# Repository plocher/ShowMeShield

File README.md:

# ShowMeShield
## License: Creative Commons Attribution-ShareAlike 2.0 Generic (CC BY-SA 2.0)

Arduino IO pin LEDs on wings

Features
  * increased board size from 5cmX5cm to 3.5"x2" - small size cut into Arduino header pads, now room for small breadboard
  * moved LEDs outside of headers, allowing visibility even if board is in middle of a shield stack
  * added a reset button because one on Arduino will be hidden by the wide wings on this board

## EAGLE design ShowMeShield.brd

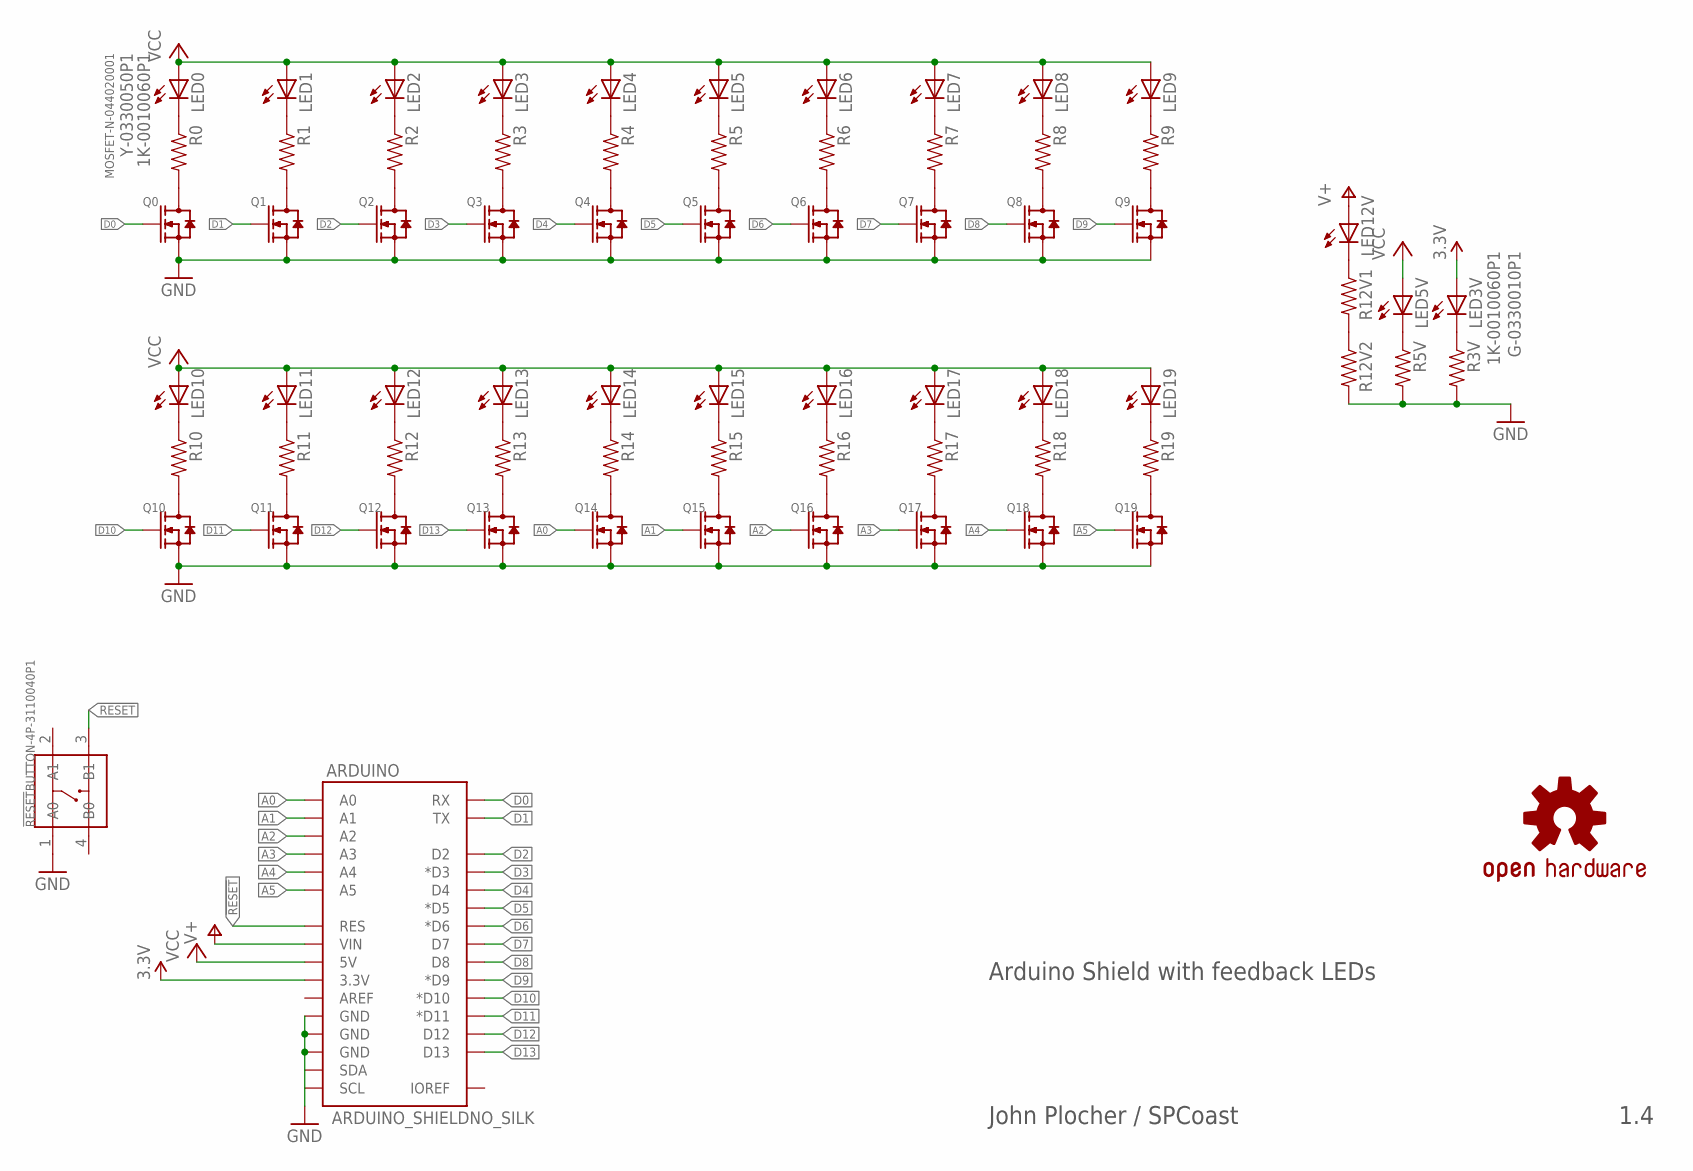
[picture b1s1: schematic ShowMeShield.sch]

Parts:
!RESET: BUTTON-4P-3110040P1; 4P-6.0X6.0X5.0H
ARDUINO: ARDUINO_SHIELDNO_SILK; DUEMILANOVE_VIAS
LED0, LED1, LED2, LED3, LED4, LED5, LED6, LED7, LED8, LED9, LED10, LED11, LED12, LED13, LED14, LED15, LED16, LED17, LED18, LED19: Y-0330050P1; CHIPLED_0603
LED3V, LED5V, LED12V: G-0330010P1; CHIPLED_0603
Q0, Q1, Q2, Q3, Q4, Q5, Q6, Q7, Q8, Q9, Q10, Q11, Q12, Q13, Q14, Q15, Q16, Q17, Q18, Q19: MOSFET-N-044020001; SOT23
R0, R1, R2, R3, R3V, R4, R5, R5V, R6, R7, R8, R9, R10, R11, R12, R12V1, R12V2, R13, R14, R15, R16, R17, R18, R19: 1K-0010060P1; 0603-RES
U$1: OSHW-LOGOM; OSHW-LOGO-M

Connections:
3.3V: ARDUINO.3.3V, LED3V.A
!RESET: !RESET.3 (B1), ARDUINO.RES
A0: ARDUINO.A0, Q14.1 (G)
A1: ARDUINO.A1, Q15.1 (G)
A2: ARDUINO.A2, Q16.1 (G)
A3: ARDUINO.A3, Q17.1 (G)
A4: ARDUINO.A4, Q18.1 (G)
A5: ARDUINO.A5, Q19.1 (G)
D0: ARDUINO.RX, Q0.1 (G)
D1: ARDUINO.TX, Q1.1 (G)
D2: ARDUINO.D2, Q2.1 (G)
D3: ARDUINO.D3 (*D3), Q3.1 (G)
D4: ARDUINO.D4, Q4.1 (G)
D5: ARDUINO.D5 (*D5), Q5.1 (G)
D6: ARDUINO.D6 (*D6), Q6.1 (G)
D7: ARDUINO.D7, Q7.1 (G)
D8: ARDUINO.D8, Q8.1 (G)
D9: ARDUINO.D9 (*D9), Q9.1 (G)
D10: ARDUINO.D10 (*D10), Q10.1 (G)
D11: ARDUINO.D11 (*D11), Q11.1 (G)
D12: ARDUINO.D12, Q12.1 (G)
D13: ARDUINO.D13, Q13.1 (G)
GND: !RESET.1 (A0), ARDUINO.GND@0 (GND), ARDUINO.GND@1 (GND), ARDUINO.GND@2 (GND), Q0.2 (S), Q1.2 (S), Q2.2 (S), Q3.2 (S), Q4.2 (S), Q5.2 (S), Q6.2 (S), Q7.2 (S), Q8.2 (S), Q9.2 (S), Q10.2 (S), Q11.2 (S), Q12.2 (S), Q13.2 (S), Q14.2 (S), Q15.2 (S), Q16.2 (S), Q17.2 (S), Q18.2 (S), Q19.2 (S), R3V.2, R5V.2, R12V2.2
unnamed: LED3V.C, R3V.1
unnamed: LED1.C, R1.1
unnamed: LED2.C, R2.1
unnamed: LED3.C, R3.1
unnamed: LED4.C, R4.1
unnamed: LED5.C, R5.1
unnamed: LED6.C, R6.1
unnamed: LED5V.C, R5V.1
unnamed: LED7.C, R7.1
unnamed: R12V1.2, R12V2.1
unnamed: LED8.C, R8.1
unnamed: LED9.C, R9.1
unnamed: LED10.C, R10.1
unnamed: LED11.C, R11.1
unnamed: LED12.C, R12.1
unnamed: LED13.C, R13.1
unnamed: LED14.C, R14.1
unnamed: LED15.C, R15.1
unnamed: LED16.C, R16.1
unnamed: LED17.C, R17.1
unnamed: LED18.C, R18.1
unnamed: LED19.C, R19.1
unnamed: LED12V.C, R12V1.1
unnamed: LED0.C, R0.1
unnamed: Q0.3 (D), R0.2
unnamed: Q1.3 (D), R1.2
unnamed: Q2.3 (D), R2.2
unnamed: Q3.3 (D), R3.2
unnamed: Q4.3 (D), R4.2
unnamed: Q5.3 (D), R5.2
unnamed: Q6.3 (D), R6.2
unnamed: Q7.3 (D), R7.2
unnamed: Q8.3 (D), R8.2
unnamed: Q9.3 (D), R9.2
unnamed: Q13.3 (D), R13.2
unnamed: Q10.3 (D), R10.2
unnamed: Q11.3 (D), R11.2
unnamed: Q12.3 (D), R12.2
unnamed: Q14.3 (D), R14.2
unnamed: Q15.3 (D), R15.2
unnamed: Q16.3 (D), R16.2
unnamed: Q17.3 (D), R17.2
unnamed: Q18.3 (D), R18.2
unnamed: Q19.3 (D), R19.2
V+: ARDUINO.VIN, LED12V.A
VCC: ARDUINO.5V, LED0.A, LED1.A, LED2.A, LED3.A, LED4.A, LED5.A, LED5V.A, LED6.A, LED7.A, LED8.A, LED9.A, LED10.A, LED11.A, LED12.A, LED13.A, LED14.A, LED15.A, LED16.A, LED17.A, LED18.A, LED19.A

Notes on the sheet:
1.4
John Plocher / SPCoast
Arduino Shield with feedback LEDs

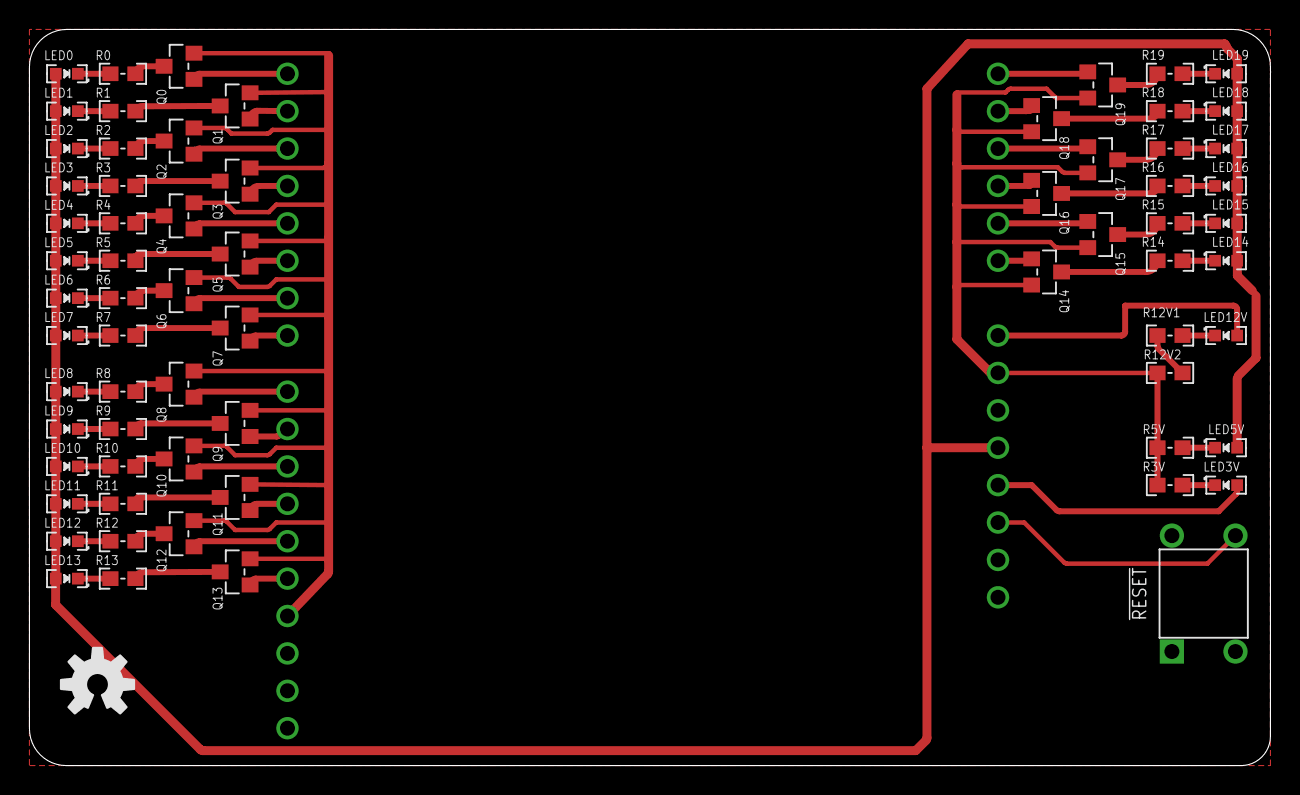
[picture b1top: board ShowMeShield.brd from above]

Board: 2 copper layers, 84.3 x 50.0 mm, 70 parts (0 on the bottom side), 69 nets.

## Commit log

2020-05-04 updated tags

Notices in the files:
ShowMeShield.brd:
CC-by-SA License
